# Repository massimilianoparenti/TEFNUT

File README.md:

# TEFNUT
Open-source, low-power temperature, humidity, and VOC sensor with E-Ink display and LoRa connectivity. Battery-powered and designed for both indoor and outdoor use, this device is ideal for smart homes, IoT applications, and environmental monitoring. Easy deployment, high efficiency, and full customization.

**DESCRIPTION**

This project aims to create a simple, low-power temperature, humidity, and VOC sensor with long-range connectivity. At its core, it features an E-Ink display for excellent readability even in direct sunlight, while LoRa communication ensures seamless integration with home automation systems and other IoT applications.

Powered by a battery, this device is built for versatility and easy deployment in both indoor and outdoor environments. It focuses on efficiency and simplicity to provide an accessible and practical solution for monitoring temperature, humidity, air quality, and gas presence.

Best of all, it’s fully open source—anyone can modify, improve, or adapt it to their needs.

If this sounds interesting, stay tuned for updates!

**REPOSITORY MAP**

**CONTRIBUTORS**

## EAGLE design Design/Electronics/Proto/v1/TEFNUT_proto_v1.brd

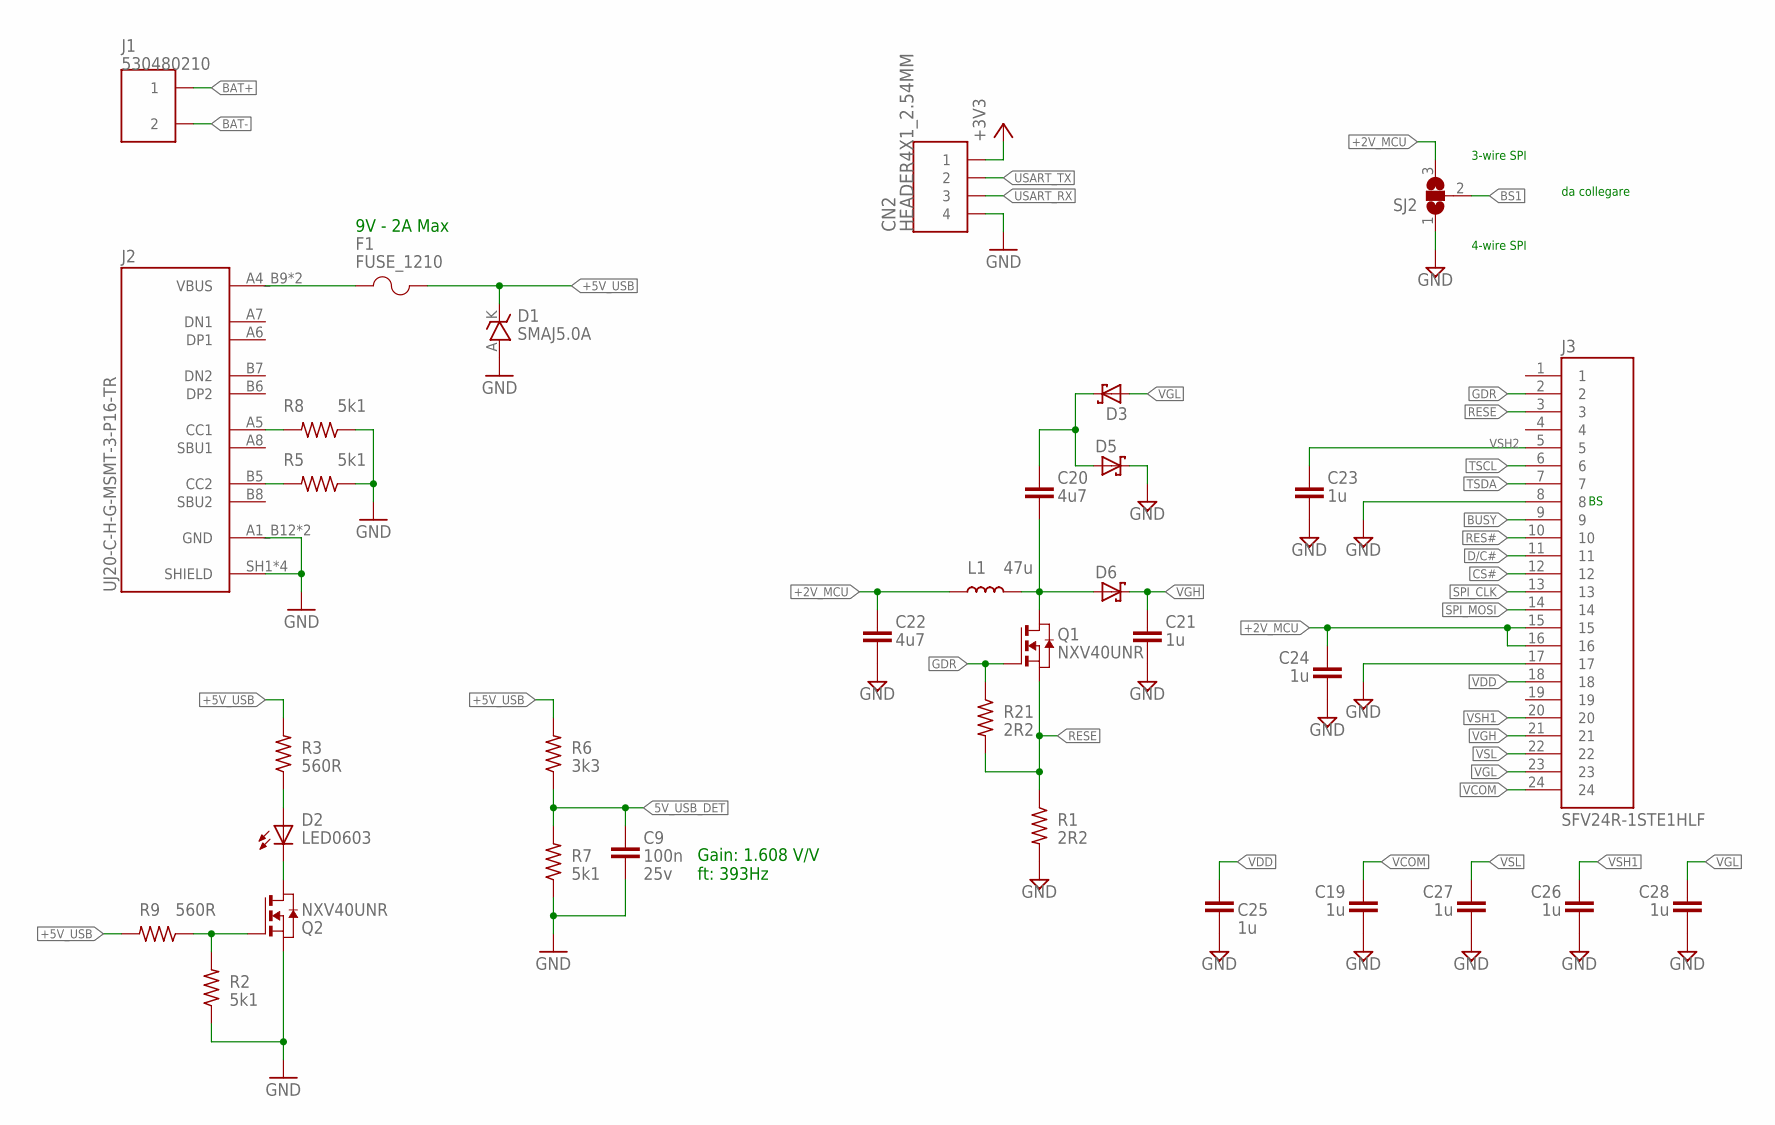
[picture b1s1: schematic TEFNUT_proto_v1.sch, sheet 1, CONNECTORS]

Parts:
C9: 100n; C0603[1608]; PARTNO CL10B104KO8NNNC
C19, C21, C23, C24, C25, C26, C27, C28: 1u; C0603[1608]; PARTNO CL10A105KO8NNNC
C20, C22: 4u7; C0603[1608]; PARTNO CL10A475KO8NNNC
CN2: HEADER4X1_2.54MM
D1: TVS214AC; DO-214AC; PARTNO SMAJ5.0A
D2: LED0603
D3, D5, D6: SCHOTTKY_DIODE_SOD123; SOD123; PARTNO MBR0530
F1: FUSE_1210; R1210[3225]; PARTNO SMD1210B110TF/16
J1: 530480210; PARTNO 530480210
J2: UJ20-C-H-G-MSMT-3-P16-TR; SAMESKY_UJ20-C-H-G-MSMT-3-P16-TR; PARTNO UJ20-C-H-G-MSMT-3-P16
J3: SFV24R-1STE1HLF; AMPHENOL_SFV24R-1STE1HLF; PARTNO SFV24R-1STE1HLF
L1: 47u; L0805[2012]; PARTNO MLF2012E100JT000
Q1, Q2: NXV40UNR; SOT23-3; PARTNO NXV40UNR
R1, R21: 2R2; R0603; PARTNO ERJ-U03F2R20V
R2, R5, R7, R8: 5k1; R0603; PARTNO RC0603FR-075K1L
R3, R9: 560R; R0603; PARTNO RC0603FR-07560RL
R6: 3k3; R0603; PARTNO RC0603FR-073K3L
SJ2: SJ2W; SJ_2

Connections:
5V_USB_DET: C9.1, R6.1, R7.2; also elsewhere on the board
+2V_MCU: C22.1, C24.1, J3.15, J3.16, L1.1, SJ2.3; also elsewhere on the board
+3V3: CN2.1
+5V_USB: D1.K, F1.2, R3.2, R6.2, R9.2; also elsewhere on the board
BAT+: J1.1; also elsewhere on the board
BAT-: J1.2; also elsewhere on the board
BS1: SJ2.2
BUSY: J3.9; also elsewhere on the board
CS#: J3.12; also elsewhere on the board
D/C#: J3.11; also elsewhere on the board
GDR: J3.2, Q1.1 (G), R21.1
GND: C9.2, C19.2, C21.2, C22.2, C23.2, C24.2, C25.2, C26.2, C27.2, C28.2, CN2.4, D1.A, D5.K, J2.A1_B12 (GND), J2.B1_A12 (GND), J2.SH1 (SHIELD), J2.SH2 (SHIELD), J2.SH3 (SHIELD), J2.SH4 (SHIELD), J3.8, J3.17, Q2.2 (S), R1.2, R2.1, R5.1, R7.1, R8.1, SJ2.1; also elsewhere on the board
unnamed: D2.2 (K), Q2.3 (D)
unnamed: D2.1 (A), R3.1
unnamed: J2.A5 (CC1), R8.2
unnamed: J2.B5 (CC2), R5.2
unnamed: F1.1, J2.A4_B9 (VBUS), J2.B4_A9 (VBUS)
unnamed: C20.1, D3.K, D5.A
unnamed: C20.2, D6.A, L1.2, Q1.3 (D)
unnamed: Q2.1 (G), R2.2, R9.1
RES#: J3.10; also elsewhere on the board
RESE: J3.3, Q1.2 (S), R1.1, R21.2
SPI_CLK: J3.13; also elsewhere on the board
SPI_MOSI: J3.14; also elsewhere on the board
TSCL: J3.6
TSDA: J3.7
USART_RX: CN2.3; also elsewhere on the board
USART_TX: CN2.2; also elsewhere on the board
VCOM: C19.1, J3.24
VDD: C25.1, J3.18
VGH: C21.1, D6.K, J3.21
VGL: C28.1, D3.A, J3.23
VSH1: C26.1, J3.20
VSH2: C23.1, J3.5
VSL: C27.1, J3.22

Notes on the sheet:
Gain: 1.608 V/V ft: 393Hz
9V - 2A Max
4-wire SPI
3-wire SPI
da collegare

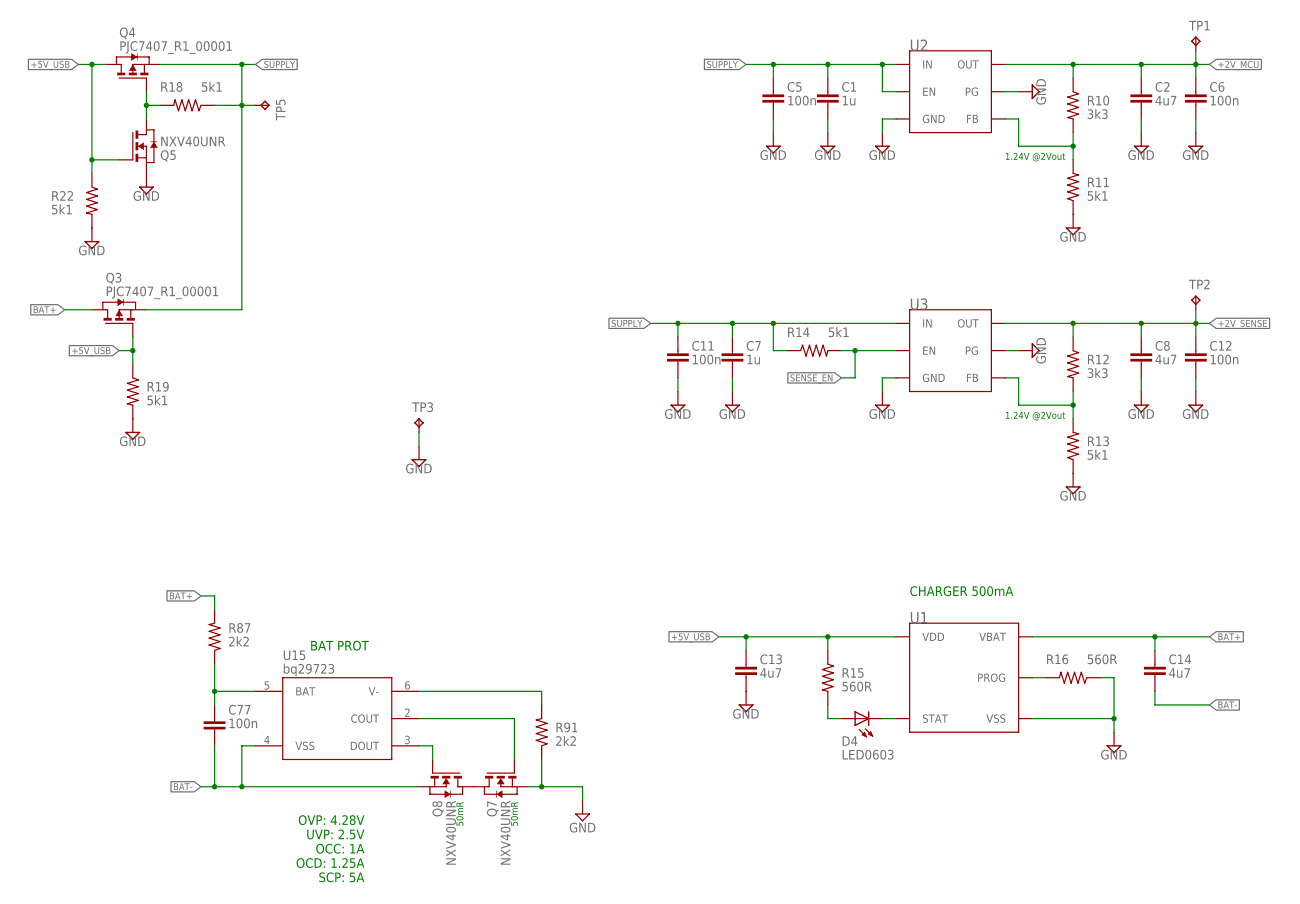
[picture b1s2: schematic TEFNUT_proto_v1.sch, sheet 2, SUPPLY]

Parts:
C1, C7: 1u; C0603[1608]; PARTNO CL10A105KO8NNNC
C2, C8: 4u7; C0603[1608]; PARTNO CL10A475KO8NNNC
C5, C6, C11, C12, C77: 100n; C0603[1608]; PARTNO CL10B104KO8NNNC
C13, C14: 4u7; C0805[2012]; PARTNO CL21A475KOFNNNE
D4: LED0603
Q3, Q4: PJC7407_R1_00001; SOT323-3(SC-70-3); PARTNO PJC7407_R1_00001
Q5, Q7, Q8: NXV40UNR; SOT23-3; PARTNO NXV40UNR
R10, R12: 3k3; R0603; PARTNO RC0603FR-073K3L
R11, R13, R14: 5k1; R0603; PARTNO RC0603FR-075K1L
R15, R16: 560R; R0603; PARTNO RC0603FR-07560RL
R18, R19, R22: 5k1; R0603[1608]; PARTNO RC0603FR-075K1L
R87, R91: 2k2; R0603; PARTNO ERJ-3EKF2201V
TP1, TP2, TP3, TP5: TPB1,27; B1,27
U1: MCP73831T; SOT23-5; PARTNO MCP73831T-2DCI/OT
U2, U3: TPS7A2501DRVRDRV0006A-IPC_B; 6-WDFN; PARTNO TPS7A2501DRVR
U15: bq29723; WSON6; PARTNO BQ29704DSER

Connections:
+2V_MCU: C2.1, C6.1, R10.1, TP1.TP, U2.1 (OUT); also elsewhere on the board
+2V_SENSE: C8.1, C12.1, R12.1, TP2.TP, U3.1 (OUT); also elsewhere on the board
+5V_USB: C13.1, Q3.1 (G), Q4.3 (D), Q5.1 (G), R15.1, R19.1, R22.1, U1.4 (VDD); also elsewhere on the board
BAT+: C14.1, Q3.3 (D), R87.2, U1.3 (VBAT); also elsewhere on the board
BAT-: C14.2, C77.2, Q8.2 (S), U15.4 (VSS); also elsewhere on the board
GND: C1.2, C2.2, C5.2, C6.2, C7.2, C8.2, C11.2, C12.2, C13.2, Q5.2 (S), Q7.2 (S), R11.1, R13.1, R16.1, R19.2, R22.2, R91.1, TP3.TP, U1.2 (VSS), U2.3 (PG), U2.5 (GND), U2.7 (GND), U3.3 (PG), U3.5 (GND), U3.7 (GND); also elsewhere on the board
unnamed: C77.1, R87.1, U15.5 (BAT)
unnamed: D4.1 (A), R15.2
unnamed: R10.2, R11.2, U2.2 (FB)
unnamed: R12.2, R13.2, U3.2 (FB)
unnamed: R16.2, U1.5 (PROG)
unnamed: D4.2 (K), U1.1 (STAT)
unnamed: Q4.1 (G), Q5.3 (D), R18.2
unnamed: R91.2, U15.6 (V-)
unnamed: Q7.3 (D), Q8.3 (D)
unnamed: Q7.1 (G), U15.2 (COUT)
unnamed: Q8.1 (G), U15.3 (DOUT)
SENSE_EN: R14.2, U3.4 (EN); also elsewhere on the board
SUPPLY: C1.1, C5.1, C7.1, C11.1, Q3.2 (S), Q4.2 (S), R14.1, R18.1, TP5.TP, U2.4 (EN), U2.6 (IN), U3.6 (IN)

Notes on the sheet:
OVP: 4.28V UVP: 2.5V OCC: 1A OCD: 1.25A SCP: 5A
1.24V @2Vout
BAT PROT
CHARGER 500mA
50mR

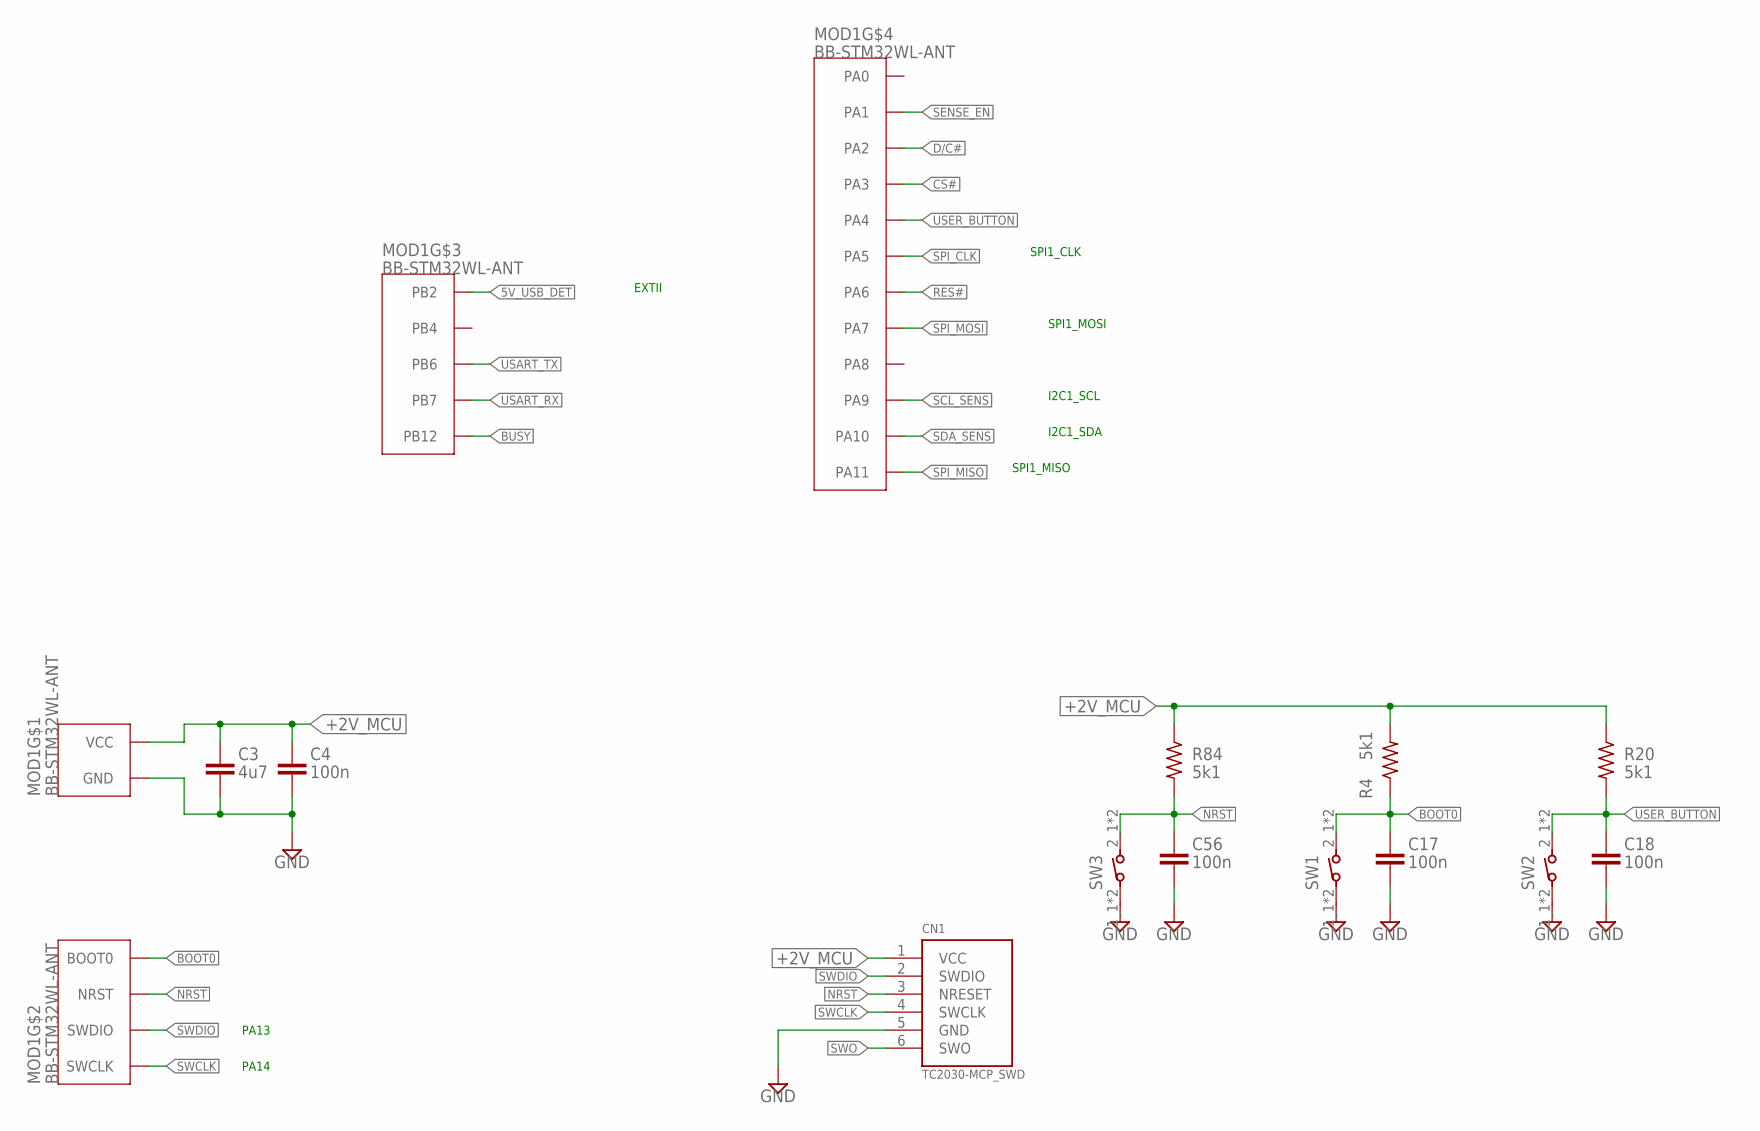
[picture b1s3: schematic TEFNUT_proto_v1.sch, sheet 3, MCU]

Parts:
C3: 4u7; C0805[2012]; PARTNO CL21A475KOFNNNE
C4: 100n; C0805[2012]; PARTNO CC0805KRX7R7BB104
C17, C18, C56: 100n; C0603[1608]; PARTNO CL10B104KO8NNNC
CN1: TC2030-MCP_SWD; TC2030-IDC
MOD1: BB-STM32WL-ANT
R4, R20, R84: 5k1; R0603; PARTNO RC0603FR-075K1L
SW1, SW2, SW3: SWITCHEVQ_4PIN; EVQ-P7L01P; PARTNO EVQP7L01P

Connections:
5V_USB_DET: MOD1.PB2; also elsewhere on the board
+2V_MCU: C3.1, C4.1, CN1.1 (VCC), MOD1.VCC, R4.2, R20.1, R84.1; also elsewhere on the board
BOOT0: C17.1, MOD1.BOOT0, R4.1, SW1.2_1 (2), SW1.2_2 (2)
BUSY: MOD1.PB12; also elsewhere on the board
CS#: MOD1.PA3; also elsewhere on the board
D/C#: MOD1.PA2; also elsewhere on the board
GND: C3.2, C4.2, C17.2, C18.2, C56.2, CN1.5 (GND), MOD1.GND, MOD1.GND@2 (GND), SW1.1_1 (1), SW1.1_2 (1), SW2.1_1 (1), SW2.1_2 (1), SW3.1_1 (1), SW3.1_2 (1); also elsewhere on the board
NRST: C56.1, CN1.3 (NRESET), MOD1.NRST, R84.2, SW3.2_1 (2), SW3.2_2 (2)
RES#: MOD1.PA6; also elsewhere on the board
SCL_SENS: MOD1.PA9; also elsewhere on the board
SDA_SENS: MOD1.PA10; also elsewhere on the board
SENSE_EN: MOD1.PA1; also elsewhere on the board
SPI_CLK: MOD1.PA5; also elsewhere on the board
SPI_MISO: MOD1.PA11
SPI_MOSI: MOD1.PA7; also elsewhere on the board
SWCLK: CN1.4 (SWCLK), MOD1.SWCLK
SWDIO: CN1.2 (SWDIO), MOD1.SWDIO
SWO: CN1.6 (SWO)
USART_RX: MOD1.PB7; also elsewhere on the board
USART_TX: MOD1.PB6; also elsewhere on the board
USER_BUTTON: C18.1, MOD1.PA4, R20.2, SW2.2_1 (2), SW2.2_2 (2)

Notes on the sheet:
I2C1_SCL
I2C1_SDA
SPI1_MISO
SPI1_MOSI
SPI1_CLK
EXTII
PA14
PA13

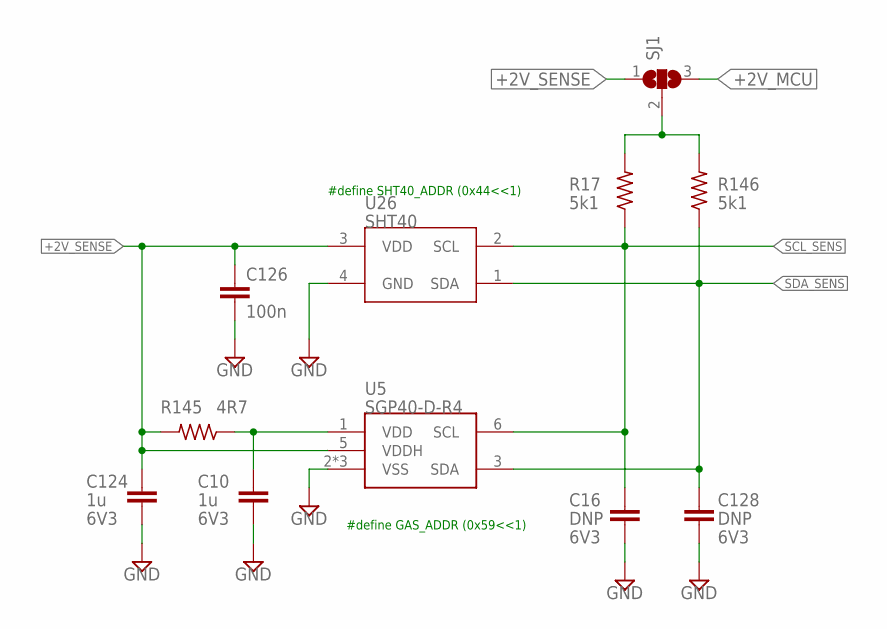
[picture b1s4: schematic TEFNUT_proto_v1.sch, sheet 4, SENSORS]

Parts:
C10, C124: 1u; C0603[1608]; PARTNO CL10A105KO8NNNC
C16, C128: DNP; C0603[1608]; PARTNO *
C126: 100n; C0603[1608]; PARTNO CL10B104KO8NNNC
R17, R146: 5k1; R0603[1608]; PARTNO RC0603FR-075K1L
R145: 4R7; R0603; PARTNO AC0603FR-072R2L
SJ1: SJ2W; SJ_2
U5: SGP40-D-R4; DFN6; PARTNO SGP40-D-R4
U26: SHT40; SH4X; PARTNO SHT40-AD1B-R3

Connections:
+2V_MCU: SJ1.3; also elsewhere on the board
+2V_SENSE: C124.2, C126.1, R145.2, SJ1.1, U5.5 (VDDH), U26.3 (VDD); also elsewhere on the board
GND: C10.1, C16.1, C124.1, C126.2, C128.1, U5.2 (VSS), U5.4 (VSS), U5.7 (VSS), U26.4 (GND); also elsewhere on the board
unnamed: R17.2, R146.2, SJ1.2
unnamed: C10.2, R145.1, U5.1 (VDD)
SCL_SENS: C16.2, R17.1, U5.6 (SCL), U26.2 (SCL); also elsewhere on the board
SDA_SENS: C128.2, R146.1, U5.3 (SDA), U26.1 (SDA); also elsewhere on the board

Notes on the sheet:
#define SHT40_ADDR (0x44<<1)
#define GAS_ADDR (0x59<<1)

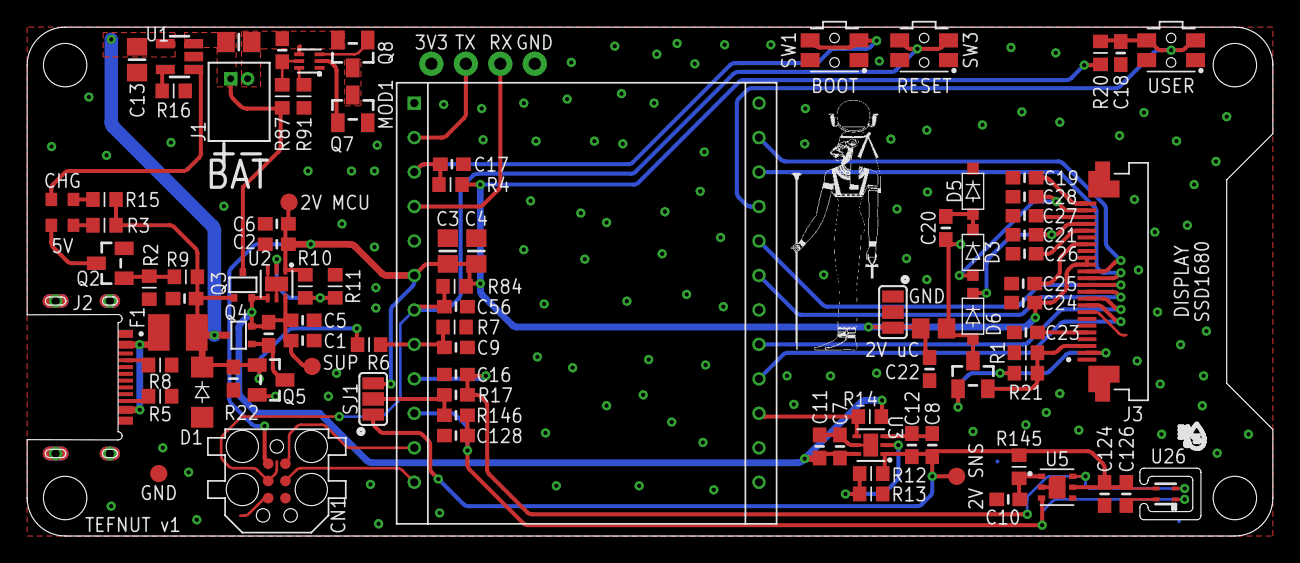
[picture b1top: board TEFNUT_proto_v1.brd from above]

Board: 2 copper layers, 91.8 x 37.5 mm, 95 parts (0 on the bottom side), 54 nets.

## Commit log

2025-04-02 Update README.md
    - Added project description
2025-04-02 Update README.md
    - Aggiunto grassetto ai titoli
2025-04-02 - Added schematic and board files - Added 3D board file

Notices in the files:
parts and their libraries:
COPYRIGHT: Copyright (C) 2025 Ultra Librarian. All rights reserved.
